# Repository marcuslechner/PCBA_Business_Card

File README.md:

# Lechnology-PCBA Business Card

This repository contains the KiCad design files for the **Lechnology Engineering** business card created by Marcus Lechner. The project blends form and function, showcasing a sleek, professional aesthetic while highlighting electrical and embedded design capabilities.

## 📐 Project Overview

The Lechnology business card is a functional PCB designed to demonstrate engineering expertise and creativity. It serves as a unique hardware portfolio piece, combining embedded systems design, elegant layout, and practical contact sharing.

## 🧠 Inspiration & References

This project was inspired by several innovative creators in the hardware and maker community. Their work served as valuable reference material throughout the development process:

- **Anthony Kouttron**  
  GitHub: [anthonykouttron/pcb-business-card-qr-nfc](https://github.com/anthonykouttron/pcb-business-card-qr-nfc)

- **Scott Atkins**  
  GitHub: [kins-dev/PCB-Card](https://github.com/kins-dev/PCB-Card)

- **Rahim Aziz**  
  GitHub: [Raziz1/PCB_Business_Card](https://github.com/Raziz1/PCB_Business_Card)

## 🛠️ Tools Used

- KiCad (PCB Design Suite)
- Custom scripts and design assets (coming soon)

## 📏 Useful Calculators

These tools were used to calculate antenna inductance for the inscribed hexagon coil:

- [Planar Coil Inductance Calculator – TranslatorsCafe](https://www.translatorscafe.com/unit-converter/sq/calculator/planar-coil-inductance/)
- [Planar Coil Inductance Calculator – Circuits.dk](https://www.circuits.dk/calculator_planar_coil_inductor.htm)

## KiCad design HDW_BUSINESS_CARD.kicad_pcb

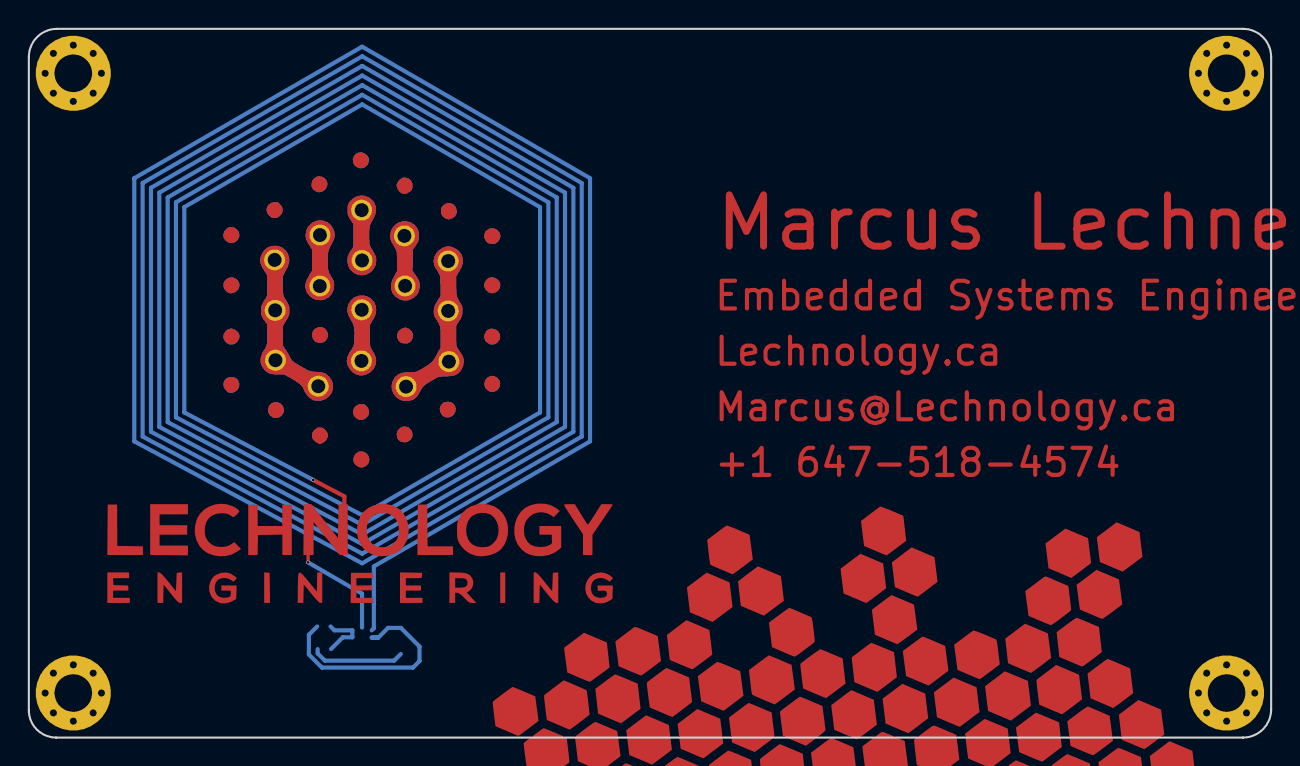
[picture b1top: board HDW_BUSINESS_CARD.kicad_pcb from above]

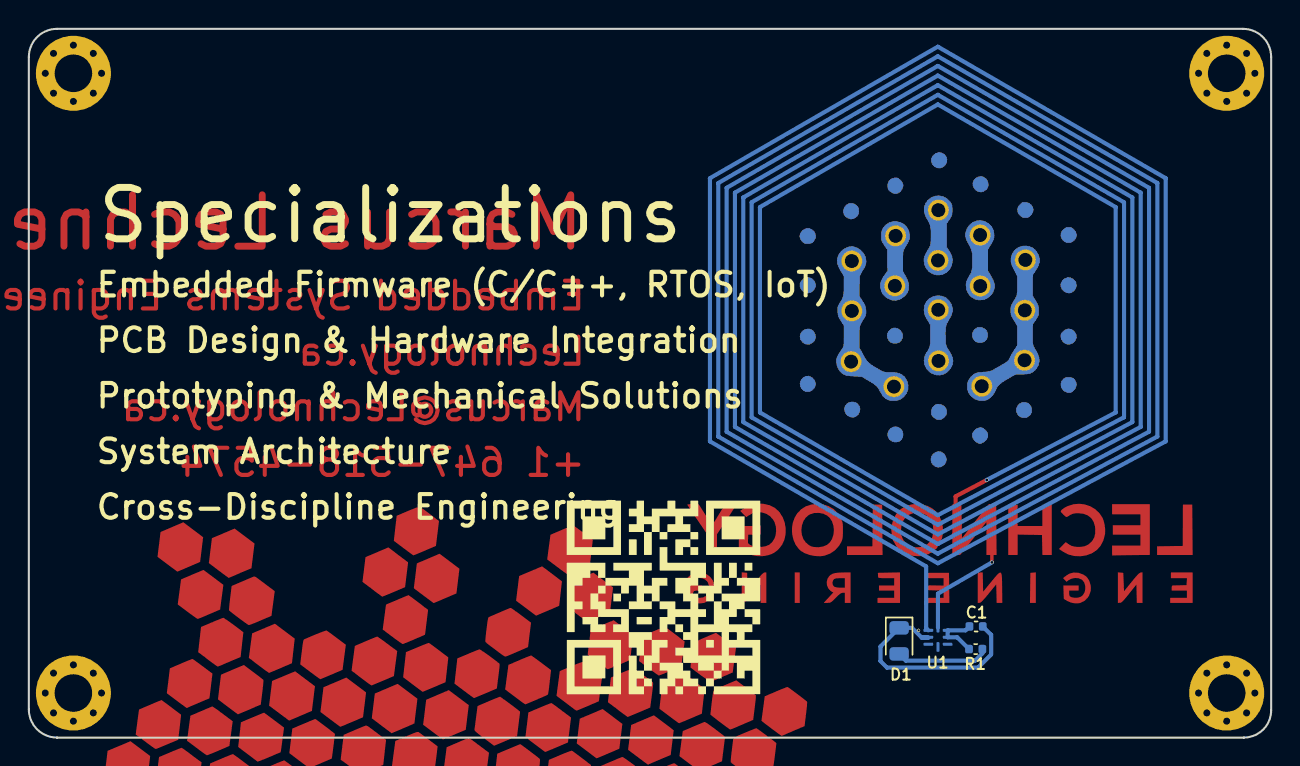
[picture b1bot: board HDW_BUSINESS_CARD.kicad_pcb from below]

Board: 2 copper layers, 89.4 x 51.0 mm, 4 parts (4 on the bottom side), 3 nets.

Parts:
C1: 220nF; C_0402_1005Metric
D1: LED; D_0805_2012Metric
R1: 47ohm; C_0402_1005Metric
U1: NT3H1101; QFN8P50_160X160X50L40X20N

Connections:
unnamed: D1.2 (A), R1.2
unnamed: C1.2, D1.1 (K), U1.2 (VSS)
unnamed: C1.1, R1.1, U1.6 (VCC), U1.7 (VOUT)

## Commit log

2025-04-12 adding License
2025-04-12 updated readme to include credit where its due
2025-04-12 created project based off anthonykouttron/pcb-business-card-qr-nfc
2025-04-18 additional changes to art work
    have a good idea of what I want to do
    going to keep it simple for now
    still waiting on final logo
    back side needs work
2025-04-19 changed specialization text to silk screen, removed lechnology text from back, arranged logo
2025-04-27 ready for NFC coil development
2025-04-27 added relevant NFC coil calculation linke
2025-04-27 added scripts directory to hold necessary pcb python scripts, currently just has script of generating a pcb hex coil
2025-04-27 added output folder to hold gerbers and drill files.
2025-04-27 nfc coil generation script complete, for visualization only
2025-04-28 switched dimension to take inscribed hexagon dimension, also fixed resistance calculation and double checked results with online trace resistance calculator
2025-04-28 can draw helical coil, thickness and gaps are messed up now
2025-04-28 submitted to PCBWay, still need to update BOM with proper components and PCB coil
2025-04-28 generating output files for first pcbway submission
2025-04-29 hexagon coil generation script works well
    added in two styles of coil
    style 0: diameter decreases every section
    style 1: diameter decreases every turn
    double checked units in kicad, style 1 is the most accurate, style 0 diameters is off by 0.1mm
2025-04-29 setup hex coil nets
2025-04-30 now I actualy set up net classes for the coil properly
2025-05-02 sending off to PCBWay for first order
2025-05-03 added mounting holes in corners
2025-05-03 works with any polygon now. Also added instructions on how to use it
2025-05-03 including .dxf files from gitignore
2025-05-03 cleaned up output before adding to git ignore
2025-05-03 ignoring output directory
2025-05-07 adjusted back mask to not be overlapped with silkscreen
2025-12-04 removed C2
2025-12-04 sumbitted to PCBWay for production
